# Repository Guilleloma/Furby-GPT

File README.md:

# Hacked Furby as a Desktop Assistant with Voice Control

https://github.com/Guilleloma/Furby-GPT/assets/115458145/2f7d8e4b-0d95-4262-baf4-6ca00bf8f71c

## Description
This project transforms a 1998 Furby into an interactive and advanced desktop assistant using a Raspberry Pi W. It incorporates OpenAI and Google Speech to text for natural language processing, primarily relying on Google Cloud Text to Speech for voice generation. It uses Picovoice's Porcupine library for voice activation and controls the Furby's motor for a dynamic user experience.

> **More on the web:** the [project page](https://makerisland.es/projects/furby-gpt) tells the full story, and [FurbyBoard por dentro](https://makerisland.es/projects/furby-gpt/placa) (in Spanish) is an interactive walkthrough of the custom board: every block animated, simulated signals and how to diagnose faults. The board's design files and datasheet live in [`Hardware/FurbyBoard/`](Hardware/FurbyBoard/README.md).

## Features
- **Function:** Designed to act as an interactive desktop assistant.
- **Platform:** Operates on a Raspberry Pi W.
- **Motor Control:** Animates the Furby in response to voice interactions.
- **Intelligent Interaction:** Processes natural language using OpenAI and Whisper/Google Speech to Text.
- **Voice Generation:** Primarily uses Google Cloud Text to Speech for verbal responses.
- **Voice Activation:** Utilizes Picovoice's Porcupine for detecting wake words.

## Requirements
- A 1998-2000 Furby.
- Raspberry Pi W (with necessary accessories).
- HAT Audio: WM8960 Audio HAT
- L298N H-Bridge (motor driver)
- Speaker (default speaker is useful as well but very poor)
- Access to OpenAI, Google Cloud & Picovoice (Elevenlabs optional)
- Knowledge in programming and electronics.

## Setup and Installation
1. **Hardware Preparation:** Modification and integration of the Raspberry Pi W into the Furby.
2. **Software Configuration:**
   - Installation and setup of OpenAI, Google Cloud
   - Installation of dependencies. Example:
     ```
     pip install openai whisper google-cloud-texttospeech pvporcupinewrapper python-dotenv
     ```
   - Add YOUR API Keys (see **Configuration** below)
3. **Programming and Integration:** Development of code to manage voice interaction and movement.

## Configuration
API keys are read from environment variables. Copy `.env.example` to `.env` and fill it in:
```
cp .env.example .env
```

| Variable | Required | Service |
|----------|----------|---------|
| `OPENAI_API_KEY` | Yes | OpenAI (Whisper and ChatGPT) |
| `PICOVOICE_ACCESS_KEY` | Yes | Picovoice Porcupine (wake word) |
| `GOOGLE_APPLICATION_CREDENTIALS` | Yes | Path to your Google Cloud service account JSON (Text-to-Speech) |
| `PICOVOICE_KEYWORD_PATH` | No | Path to your wake word model (`.ppn`). Defaults to `heymatepicovoice.ppn` next to the scripts |
| `ELEVENLABS_API_KEY` | Only with ElevenLabs | ElevenLabs (optional TTS) |
| `ELEVENLABS_VOICE_ID` | Only with ElevenLabs | ID of the ElevenLabs voice to use |

`.env` is loaded automatically when `python-dotenv` is installed; otherwise export the variables in your shell. `.env` is in `.gitignore`: never commit it. If a variable is missing, the program stops and tells you which one.

The wake word model is created in the Picovoice Console and is tied to your account, so `*.ppn` files are not committed: download yours and place it next to the scripts or set `PICOVOICE_KEYWORD_PATH`.

### Furby personality
The system prompt lives in `chatbot1.txt`, which is local and ignored by git. Create it from the example and personalise it:
```
cp chatbot1.example.txt chatbot1.txt
```
If `chatbot1.txt` does not exist, the program uses `chatbot1.example.txt` and prints a warning. Keep personal details in `chatbot1.txt` only.

## Usage
1. Wake up the Furby with a keyword using Porcupine.
2. Interact with the Furby, which uses Whisper and OpenAI for understanding and responding.
3. Enjoy the Furby's responses and animations, controlled by the Raspberry Pi W.

## Contribution
To contribute to the project:
```
1. Fork the project
2. Create your feature branch (`git checkout -b feature/AmazingFeature`)
3. Commit your changes (`git commit -m 'Add some AmazingFeature'`)
4. Push to the branch (`git push origin feature/AmazingFeature`)
5. Open a Pull Request
```

## License
This project is licensed under the MIT License - see the LICENSE.md file for details.

## Contact
Contact information of the project creator.

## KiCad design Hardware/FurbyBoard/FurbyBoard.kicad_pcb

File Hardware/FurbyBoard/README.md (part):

# FurbyBoard v1.0: hoja de datos

> **Explicación interactiva de cada bloque, con señales y diagnóstico:** [makerisland.es/projects/furby-gpt/placa](https://makerisland.es/projects/furby-gpt/placa)

Placa principal del Furby-GPT: va atornillada en el suelo de la base de un Furby de 1998 y sustituye a su electrónica. Lleva un ESP32-S3 con WiFi, cámara, micro y altavoz, mueve el motor original del mecanismo, lee los sensores del muñeco y se alimenta de una LiPo de una celda que se carga por USB-C.

Este documento es la referencia para quien coja la placa sin contexto: qué hace cada bloque, qué hay en cada conector, qué pin usa el firmware, dónde se mide y qué límites tiene. El porqué de cada decisión está en [`NOTAS.md`](NOTAS.md); el plan de pruebas, en [`TEST-PLAN.md`](TEST-PLAN.md); las simulaciones, en [`sim/RESULTADOS.md`](sim/RESULTADOS.md). Si este documento y el esquema no coinciden, manda el esquema (`scripts/design.py`).

## Estado (2026-10-27)

| | |
|---|---|
| Versión | **v1.0** (serigrafía «v1.0 · 2026-10») |
| Rama | `feature/electronica-v1` |
| Esquema | 8 hojas, 152 referencias (126 piezas montadas por el fabricante, 52 códigos LCSC). ERC 0 errores y 0 avisos |
| PCB | 6 capas, **rutada al completo** (0 conexiones sin unir). DRC con paridad esquema-PCB: 0 errores, 0 avisos. `pcb-toolkit revisar-rutado`: PASS, 0 errores |
| Puertas pasadas | A (arquitectura), B (esquema), C (colocación, con revisión independiente), D (rutado, propia), S (serigrafía), **E1** (diseño listo para fabricar, con revisión independiente) y **E2** (ficheros de fabricación). El 2026-10-27 se cerraron las mejoras **M7** (series de 33 Ω en los relojes de la cámara) y **M1** (paralelos In2/In3) con la E1 y la E2 repetidas (`revisiones/2026-10-27-M7-M1.md`); **pendiente su revisión independiente**. Informes en [`revisiones/`](revisiones/) y tabla «Revisiones» de `NOTAS.md` |
| Ficheros de fabricación | Gerber, taladros, BOM y CPL de JLCPCB en [`fabricacion/`](fabricacion/README.md), con la puerta E2 pasada (2026-10-25) y regenerados el 2026-10-27 tras M7 y M1. Antes de pedir: lista «Confirmar antes de pedir» de [`fabricacion/README.md`](fabricacion/README.md) |
| Fabricada | No. Nadie ha medido todavía una placa real: todo lo que sigue es diseño y simulación |
| Firmware | No existe. Las reglas que debe cumplir están en «Reglas para el firmware» |

## Resumen

| Característica | Valor |
|----------------|-------|
| Tamaño | ≈ 68,8 × 74,6 mm, forma del suelo de la base; 1,6 mm de grosor |
| Fijación | 4 tornillos M2 (taladros de 2,3 mm); agujero central de Ø11,3 mm para el eje del mecanismo |
| Alimentación | USB-C de 5 V (solo carga, Rd de 5,1 kΩ) y LiPo 1S de 1400 mAh soldada a pads, con protección contra la inversión |
| Carga | BQ24073 con power path: 0,49 A de carga; entrada de 0,475 A (USB500, por defecto) o 1,34 A (ILIM) |
| Raíles | VSYS (4,4 V con USB; VBAT − 50 mV sin USB), 3V3 (2 A), V6 (5,94 V para el motor), 2V8 y 1V2 de la cámara |
| Procesador | ESP32-S3-WROOM-1-N16R8 (16 MB de flash, 8 MB de PSRAM octal), WiFi y BLE con antena de PCB |
| Motor | Puente H DRV8231A a 6 V, PWM de 20 kHz, corriente limitada a 1,0 A y medida (2,25 V/A) |
| Audio | Amplificador clase D MAX98357A (altavoz de 4 Ω, 0,9–1,9 W según la batería) y micro I2S ICS-43434 en una plaquita aparte |
| Cámara | DVP de 8 bits por FPC de 24 pines (OV2640; OV3660 u OV5640 cambiando U9), con 33 Ω en serie en XCLK (R59, junto al módulo) y en PCLK (R60, junto al FPC) |
| Sensores | Inclinación, lengua, barriga y espalda por un expansor TCA9535; leva y encoder del mecanismo, luz e infrarrojos directos al módulo |
| Depuración | 5 LED, 14 puntos de test, botones RST y BOOT, consola UART en J_EXP y 5 puentes de soldadura |
| Consumo | Dormido ≈ 80 µA; escuchando 85–120 mA; pico ≈ 2,9 A en la batería (estimado) |
| Temperatura | 0–50 °C de ambiente dentro del Furby |

## Diagrama de bloques

```
USB-C (J1) ─ ESD USBLC6 (U1) ─ PTC 1,5 A (F1) ─ VBUS ─┐
                                                       │
                          BQ24073 (U2), power path ◄───┘
                          │  BAT ◄──► Q1 SI7615ADN ◄──► J2 (BAT+) / J3 (BAT−)  LiPo 1S
                          ▼
                        VSYS 4,4 V / VBAT
        ┌──────────────┬──────┴──────────┬───────────────────┬────────────┐
        ▼              ▼                 ▼                   ▼            ▼
  TPS63802 (U3)   TPS61089 (U5)    MAX98357A (U7)     LED IR (J7)    J_EXP.3
  buck-boost      elevador          clase D → J8        por R54 y Q3
  3V3, 2 A        V6 5,94 V         (altavoz)
        │              │
        │              └─► DRV8231A (U6) → motor (J9 M1/M2)
        ├─► ESP32-S3-WROOM-1 (U4) ── I2C ── TCA9535 (U10) ── sensores (J8, J9), LED RUN, LED del encoder (EN_6V por R51), control de la potencia
        │                         ├─ I2S ── U7 y micro (J5)
        │                         ├─ DVP ── cámara (J6)
        │                         └─ USB ── J1
        ├─► ME6211 2V8 (U8) → ME6211 1V2 (U9) → cámara (J6), encendidas por el expansor
        └─► pull-ups, LED, Schmitt del encoder (U11), J_EXP.2
```

| Bloque | Piezas | Qué hace |
|--------|--------|----------|
| Entrada USB | J1, U1, F1, R1, R2 | USB-C de 16 pines de montaje medio. Rd de 5,1 kΩ en CC1 y CC2: cualquier fuente da 5 V. **La placa no lee las líneas CC**, así que no sabe cuánta corriente ofrece el cargador. D+ y D− van al USB nativo del ESP32-S3 |
| Cargador y power path | U2, R4–R7, C1–C4, RT1 | BQ24073: carga a 0,494 A (R4) con ventana de temperatura de 0–50 °C medida por la NTC RT1 bajo la batería. Arranca en USB500 (EN1 = 1, EN2 = 0); el firmware puede pasar a ILIM (1,34 A, R5). VSYS sale regulado a 4,4 V con USB y sigue a la batería sin él |
| Batería | J2, J3, Q1, R12, R13, R14, C5 | P-MOSFET SI7615ADN con la puerta a GND: con la batería al revés no llega tensión negativa a nada (probado también con USB en la simulación). Divisor 470k/470k a VBAT_SNS (ADC) |
| 3V3 | U3, L1, R15, R16, C6–C8 | Buck-boost TPS63802: 3,30 V desde VSYS (2,3–4,4 V), hasta 2 A; alimenta el módulo, el expansor, la cámara y la lógica |
| 6 V y motor | U5, L2, R20–R25, C12–C22, U6, R26–R30, JP1–JP3 | Elevador TPS61089 a 5,94 V (ILIM 3,8 A), solo encendido cuando hace falta (EN_6V). Puente H DRV8231A con ITRIP de 1,0 A (VREF por R26/R27) y salida de corriente IPROPI (2,25 V/A, R28) al ADC |
| Audio | U7, C24–C26, C41, R31, R32, J5 | MAX98357A desde VSYS, ganancia de 6 dB, controlado por AMP_SD. El micro ICS-43434 va en una plaquita con cable (≤ 15 cm) a J5; comparte BCLK y WS con el amplificador (bus I2S full duplex) |
| Cámara | J6, U8, U9, R33–R35, R59, R60, C27–C31 | FPC de 24 pines con el pinout habitual de los módulos OV2640/OV3660/OV5640 para ESP32 (**verificar con el módulo concreto**). AVDD de 2,8 V y DVDD de 1,2 V (1,5 V cambiando U9 por ME6211C15) con CAM_EN; DOVDD a 3V3 |
| Expansor y sensores | U10, R36–R52, C32–C39, U11, JP4 | TCA9535 en 0x20 sobre el I2C del módulo (el mismo bus que el SCCB de la cámara). Entradas con pull-up, 1 kΩ en serie y 100 nF; Schmitt 74LVC1G17 para el encoder |
| IR y luz | Q3, R53–R56, C40, J7 | Emisor IR con AO3400A (≈ 100 mA en pulsos por R54 de 22 Ω desde VSYS), receptor alimentado por el expansor (P17), LDR con 470 kΩ a GND |
| LED y depuración | D1–D5, R10, R11, R19, R57, R58, SW1, SW2, JP5, TP1–TP14, J11 | Ver «LED», «Botones y puentes» y «Puntos de test» |

## Capas y rutado

**6 capas, 1,6 mm, apilado JLC06161H-7628 de JLCPCB** (cobre de 1 oz fuera y 0,5 oz dentro; espesores a confirmar en el presupuesto del pedido):

| Capa | Uso | Dieléctrico debajo |
|------|-----|--------------------|
| L1 F.Cu | Todas las piezas, par USB (0,28/0,15 mm, ≈ 87 Ω diferencial) y bus de la cámara sobre GND; relleno de GND | prepreg 0,21 mm |
| L2 In1 | **GND continuo** (salvo bajo la antena) | núcleo 0,40 mm |
| L3 In2 | Señales (I2S, sensado, señales lentas bajo el módulo) con relleno de VSYS | prepreg 0,21 mm |
| L4 In3 | Señales lentas: autopistas este-oeste y norte-sur (expansor, J9, UART, IR, I2C a J_EXP) | núcleo 0,40 mm |
| L5 In4 | **GND continuo** (referencia de In3 y de B.Cu) | prepreg 0,21 mm |
| L6 B.Cu | Señales, TP, pads de cable y relleno de GND; logos y rótulos | — |

Vías pasantes de 0,6/0,3 mm (0,45/0,2 solo en el par USB); sin ciegas ni enterradas. Las vías térmicas de los pads expuestos (U2, U4, U6, U7) van rellenas y tapadas (POFV, de serie en 6 capas en JLCPCB). Toda la placa está cosida a GND entre In1, In4 y las caras exteriores (paso de ≈ 4 mm en el borde).

**Por qué 6 y no 4:** con 4 capas, el rutado crítico (lazos de los convertidores, par USB, bus de la cámara, I2S) y la colocación aprobada dejaban encerrado al expansor: 57 conexiones no tenían camino. Pasar a 6 capas (In3 de señal e In4 de GND) conservó todo lo rutado y abrió los pasillos; cuesta del orden de 15–30 USD más por pedido de 5 placas (decisión del autor del proyecto, 2026-10-24).

**Cómo está rutada:** a mano, por bloques de señales, en [`scripts/rutas_fijas.py`](scripts/rutas_fijas.py): cada pista, vía y polígono está escrito con su red, su capa y su ancho, y `gen_pcb.py` lo resuelve contra los pads reales. **No hay autorrutador** (Freerouting se probó con la colocación de 4 capas y se descartó). Lo primero fueron los lazos de potencia según el layout de referencia de cada chip, el par USB, la cámara y el I2S; después, las señales lentas por bloques (A1…U2), los arreglos de la simulación (bloque F), el cosido de GND (bloque E) y la serigrafía (bloque S). Anchos mínimos por red (tabla de raíles de `NOTAS.md`) comprobados por el DRC y por `revisar-rutado`.

## Serigrafía

- **Cara superior:** qué es cada LED, botón y puente, y «FURBYBOARD V1.0».
- **Cara inferior:** la función de cada pad de cable y los GPIO de J_EXP, el nombre de cada TP, «FurbyBoard», versión y fecha, el recuadro PLACA para numerarla y dos logos: el Furby en pixel art (esquina trasera, junto a J_EXP) y el de **@GuilleMaker** (11,0 × 10,7 mm, sobre el nombre de la placa, junto al agujero del mecanismo).
- Los rótulos y el logo de GuilleMaker se colocan por script **después del rutado**, sin pisar vías (≥ 0,15 mm), pads ni otros rótulos; el logo va el último porque es decoración. Letra de 1,0 mm (0,8 donde no cabe, ver «Limitaciones conocidas») y trazo de 0,15 mm, los mínimos de JLCPCB.
- Logo de GuilleMaker: [`scripts/logo_guillemaker.py`](scripts/logo_guillemaker.py) lo vectoriza desde [`serigrafia/logo-guillemaker.png`](serigrafia/logo-guillemaker.png); el texto mide 1,48 mm de alto con trazo de 0,18 mm. Vista de la cara inferior: [`render/serigrafia-logo-guillemaker.png`](render/serigrafia-logo-guillemaker.png).

## Conectores y pads

Las vistas «desde abajo» son como se ve la placa por la cara inferior, donde se sueldan los cables. Los pads de cable son pasantes de 2,54 mm; el pad 1 es el cuadrado.

### J1: USB-C (16 pines, HRO TYPE-C-31-M-13C)

| Pin | Red | Notas |
|-----|-----|-------|
| A4, A9, B4, B9 | VBUS_IN | 5 V; pasa por U1 (ESD) y F1 (PTC de 1,5 A) a VBUS |
| A5 / B5 | CC1 / CC2 | Rd de 5,1 kΩ a GND (R1, R2): sumidero por defecto |
| A6, B6 / A7, B7 | USB_DP / USB_DN | USB nativo del ESP32-S3 (GPIO20/19, USB Serial/JTAG); protegidos por U1 |
| A1, A12, B1, B12, carcasa | GND | |
| A8, B8 | — | SBU sin conectar |

### J2 y J3: batería

| Pad | Forma | Red | Rótulos |
|-----|-------|-----|---------|
| J2 | Cuadrado de 3 × 3 mm, taladro de 1,2 | BAT_PAD (+), antes de Q1 | «+» arriba, «BAT+» abajo |
| J3 | Redondo de Ø2,6 mm, taladro de 1,0 | GND (−) | «-» arriba, «BAT-» abajo |

Celda LiPo 1S de 1400 mAh **con PCM** y resistencia interna (con el PCM) **≤ 100 mΩ** («Reglas para el firmware»). Antes de soldarla se prueba la protección contra la inversión (`TEST-PLAN.md` §8.1).

### J5: micro I2S (2 × 3, en el borde izquierdo)

| Pad | Rótulo | Red | Pin del micro |
|-----|--------|-----|---------------|
| 1 | SD | I2S_DIN (GPIO17) | SD (datos) |
| 2 | G | GND | GND |
| 3 | SCK | I2S_SCK_MIC (BCLK por R31 de 33 Ω) | SCK |
| 4 | WS | I2S_WS_MIC (WS por R32 de 33 Ω) | WS |
| 5 | 3V3 | 3V3 | VDD |
| 6 | G | GND | GND (y L/R, según el canal elegido en la plaquita) |

La selección L/R del ICS-43434 se fija en la plaquita del micro. Cable de ≤ 15 cm.

### J6: cámara (FPC de 24 pines, paso 0,5 mm, AFC01-S24FCA-00)

En el borde derecho, pin 1 abajo, con el flex saliendo hacia la pared de la base.

| Pin | Red | Pin | Red |
|-----|-----|-----|-----|
| 1 | — | 13 | CAM_XCLK (GPIO13 por R59 de 33 Ω) |
| 2 | GND | 14 | CAM_Y8 (GPIO14) |
| 3 | I2C_SDA (SIOD) | 15 | GND |
| 4 | CAM_2V8 (AVDD) | 16 | CAM_Y7 (GPIO21) |
| 5 | I2C_SCL (SIOC) | 17 | CAM_PCLK_CAM (GPIO47 por R60 de 33 Ω) |
| 6 | CAM_RST (RC de R35/C31) | 18 | CAM_Y6 (GPIO48) |
| 7 | CAM_VSYNC (GPIO10) | 19 | CAM_Y2 (GPIO38) |
| 8 | CAM_PWDN (P15 del expansor) | 20 | CAM_Y5 (GPIO39) |
| 9 | CAM_HREF (GPIO11) | 21 | CAM_Y3 (GPIO40) |
| 10 | CAM_DVDD (1,2 V) | 22 | CAM_Y4 (GPIO41) |
| 11 | 3V3 (DOVDD) | 23, 24 | — |
| 12 | CAM_Y9 (GPIO12) | Patas | GND |

Pinout de facto de los módulos para ESP32 (OV2640/OV3660/OV5640): **compruébese con el módulo comprado antes de enchufarlo**. RESETB no da un flanco limpio al encender: el firmware resetea la cámara por SCCB.

### J7: IR y luz (2 × 4, delante a la izquierda)

| Pad | Rótulo | Red | Qué se conecta |
|-----|--------|-----|----------------|
| 1 | IR+ | IR_LED_A (VSYS por R54 de 22 Ω) | Ánodo del LED IR emisor |
| 2 | IR- | IR_LED_K (drenador de Q3, GPIO45) | Cátodo del LED IR emisor |
| 3 | G | GND | GND del receptor IR |
| 4 | RX | IR_RX_PAD (GPIO42 por R56 de 1 kΩ) | Salida del receptor IR |
| 5 | 3V3 | 3V3 | Un extremo de la LDR |
| 6 | LDR | LIGHT (GPIO2, 470 kΩ a GND) | Otro extremo de la LDR |
| 7 | G | GND | |
| 8 | RXV | IR_PWR (P17 del expansor) | Alimentación del receptor IR (se apaga para dormir) |

Leyenda en la cara inferior a la derecha de los pads, fila por fila. J7.3 y J7.8 se permutaron en el rutado (bloque U2): el receptor IR usa 8 (alimentación), 3 (GND) y 4 (salida).

### J8: inclinación, lengua y altavoz (1 × 7, borde izquierdo)

| Pad | Rótulo | Red | Qué se conecta |
|-----|--------|-----|----------------|
| 1 | TLA | TILT_A_PAD (P00, 220 kΩ de pull-up) | Contacto A del sensor de inclinación |
| 2 | TLB | TILT_B_PAD (P01, 220 kΩ) | Contacto B del sensor de inclinación |
| 3 | G | GND | Común del sensor de inclinación |
| 4 | LNG | TONGUE_PAD (P02, 47 kΩ) | Interruptor de la lengua |
| 5 | G | GND | Otro lado del interruptor de la lengua |
| 6 | SP+ | SPK_P | Altavoz + (4 Ω) |
| 7 | SP- | SPK_N | Altavoz − |

Las salidas del altavoz son las del clase D en puente (BTL): ninguna de las dos va a GND.

### J9: mecanismo, barriga y espalda (2 × 6, borde derecho)

| Pad | Rótulo | Red | Qué se conecta |
|-----|--------|-----|----------------|
| 1 | ENF | ENC_PT (10 kΩ a 3V3, Schmitt U11 → GPIO8) | Colector del fototransistor del encoder |
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
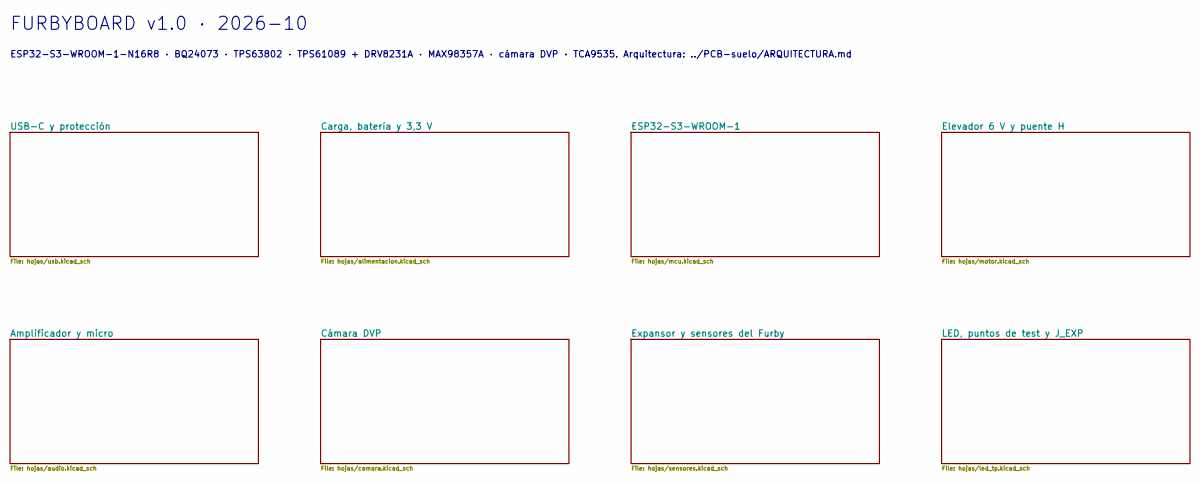
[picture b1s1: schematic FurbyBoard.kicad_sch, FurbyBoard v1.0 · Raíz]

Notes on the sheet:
FURBYBOARD v1.0 · 2026-10
ESP32-S3-WROOM-1-N16R8 · BQ24073 · TPS63802 · TPS61089 + DRV8231A · MAX98357A · cámara DVP · TCA9535. Arquitectura: ../PCB-suelo/ARQUITECTURA.md

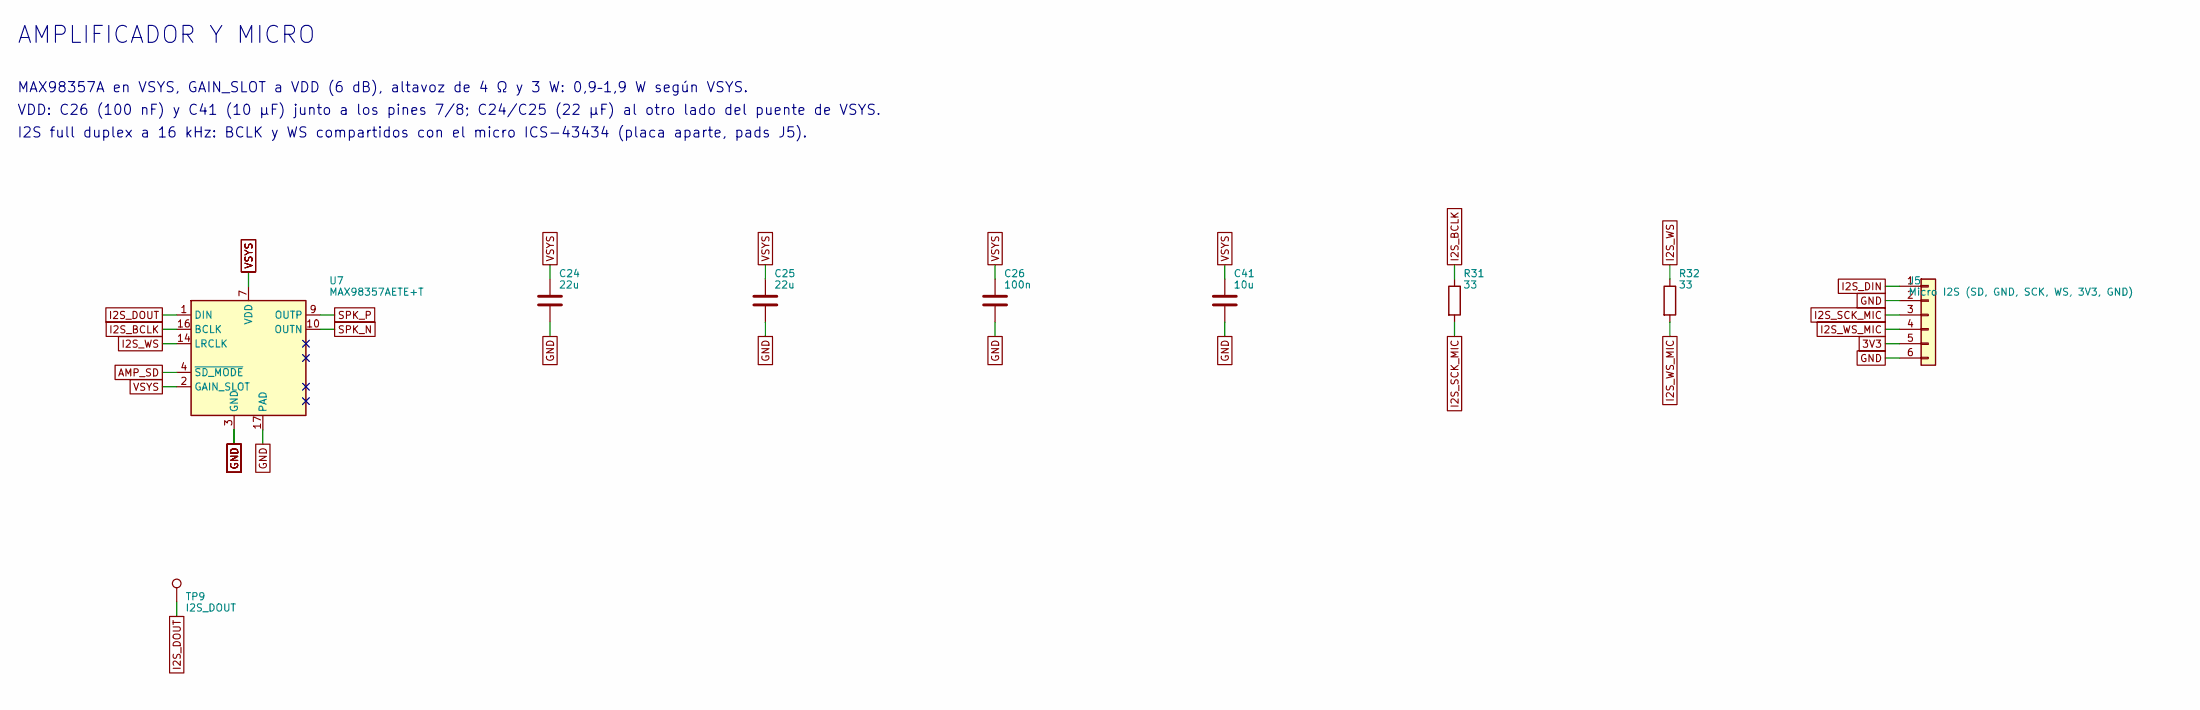
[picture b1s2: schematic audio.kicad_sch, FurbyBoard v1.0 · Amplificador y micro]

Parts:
C24, C25: 22u; C_0805_2012Metric; MPN 22 µF 25 V X5R; LCSC C45783
C26: 100n; C_0603_1608Metric; MPN 100 nF 50 V X7R; LCSC C14663
C41: 10u; C_0603_1608Metric; MPN 10 µF 10 V X5R; LCSC C19702
J5: Micro I2S (SD, GND, SCK, WS, 3V3, GND); Pads_2x03_P2.54mm
R31, R32: 33; R_0603_1608Metric; MPN UNI-ROYAL 0603 1%; LCSC C23140
TP9: I2S_DOUT; TestPoint_Pad_D1.5mm
U7: MAX98357AETE+T; TQFN-16-1EP_3x3mm_P0.5mm_EP1.23x1.23mm; MPN Maxim MAX98357AETE+T; LCSC C910544

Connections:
3V3: J5.5; also elsewhere on the board
AMP_SD: U7.4 (~SD_MODE); also elsewhere on the board
GND: C24.2, C25.2, C26.2, C41.2, J5.2, J5.6, U7.3 (GND), U7.11 (GND), U7.15 (GND), U7.17 (PAD); also elsewhere on the board
I2S_BCLK: R31.1, U7.16 (BCLK); also elsewhere on the board
I2S_DIN: J5.1; also elsewhere on the board
I2S_DOUT: TP9.1, U7.1 (DIN); also elsewhere on the board
I2S_SCK_MIC: J5.3, R31.2
I2S_WS: R32.1, U7.14 (LRCLK); also elsewhere on the board
I2S_WS_MIC: J5.4, R32.2
SPK_N: U7.10 (OUTN); also elsewhere on the board
SPK_P: U7.9 (OUTP); also elsewhere on the board
VSYS: C24.1, C25.1, C26.1, C41.1, U7.2 (GAIN_SLOT), U7.7 (VDD), U7.8 (VDD); also elsewhere on the board

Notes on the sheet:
VDD: C26 (100 nF) y C41 (10 µF) junto a los pines 7/8; C24/C25 (22 µF) al otro lado del puente de VSYS.
I2S full duplex a 16 kHz: BCLK y WS compartidos con el micro ICS-43434 (placa aparte, pads J5).
MAX98357A en VSYS, GAIN_SLOT a VDD (6 dB), altavoz de 4 Ω y 3 W: 0,9–1,9 W según VSYS.
AMPLIFICADOR Y MICRO

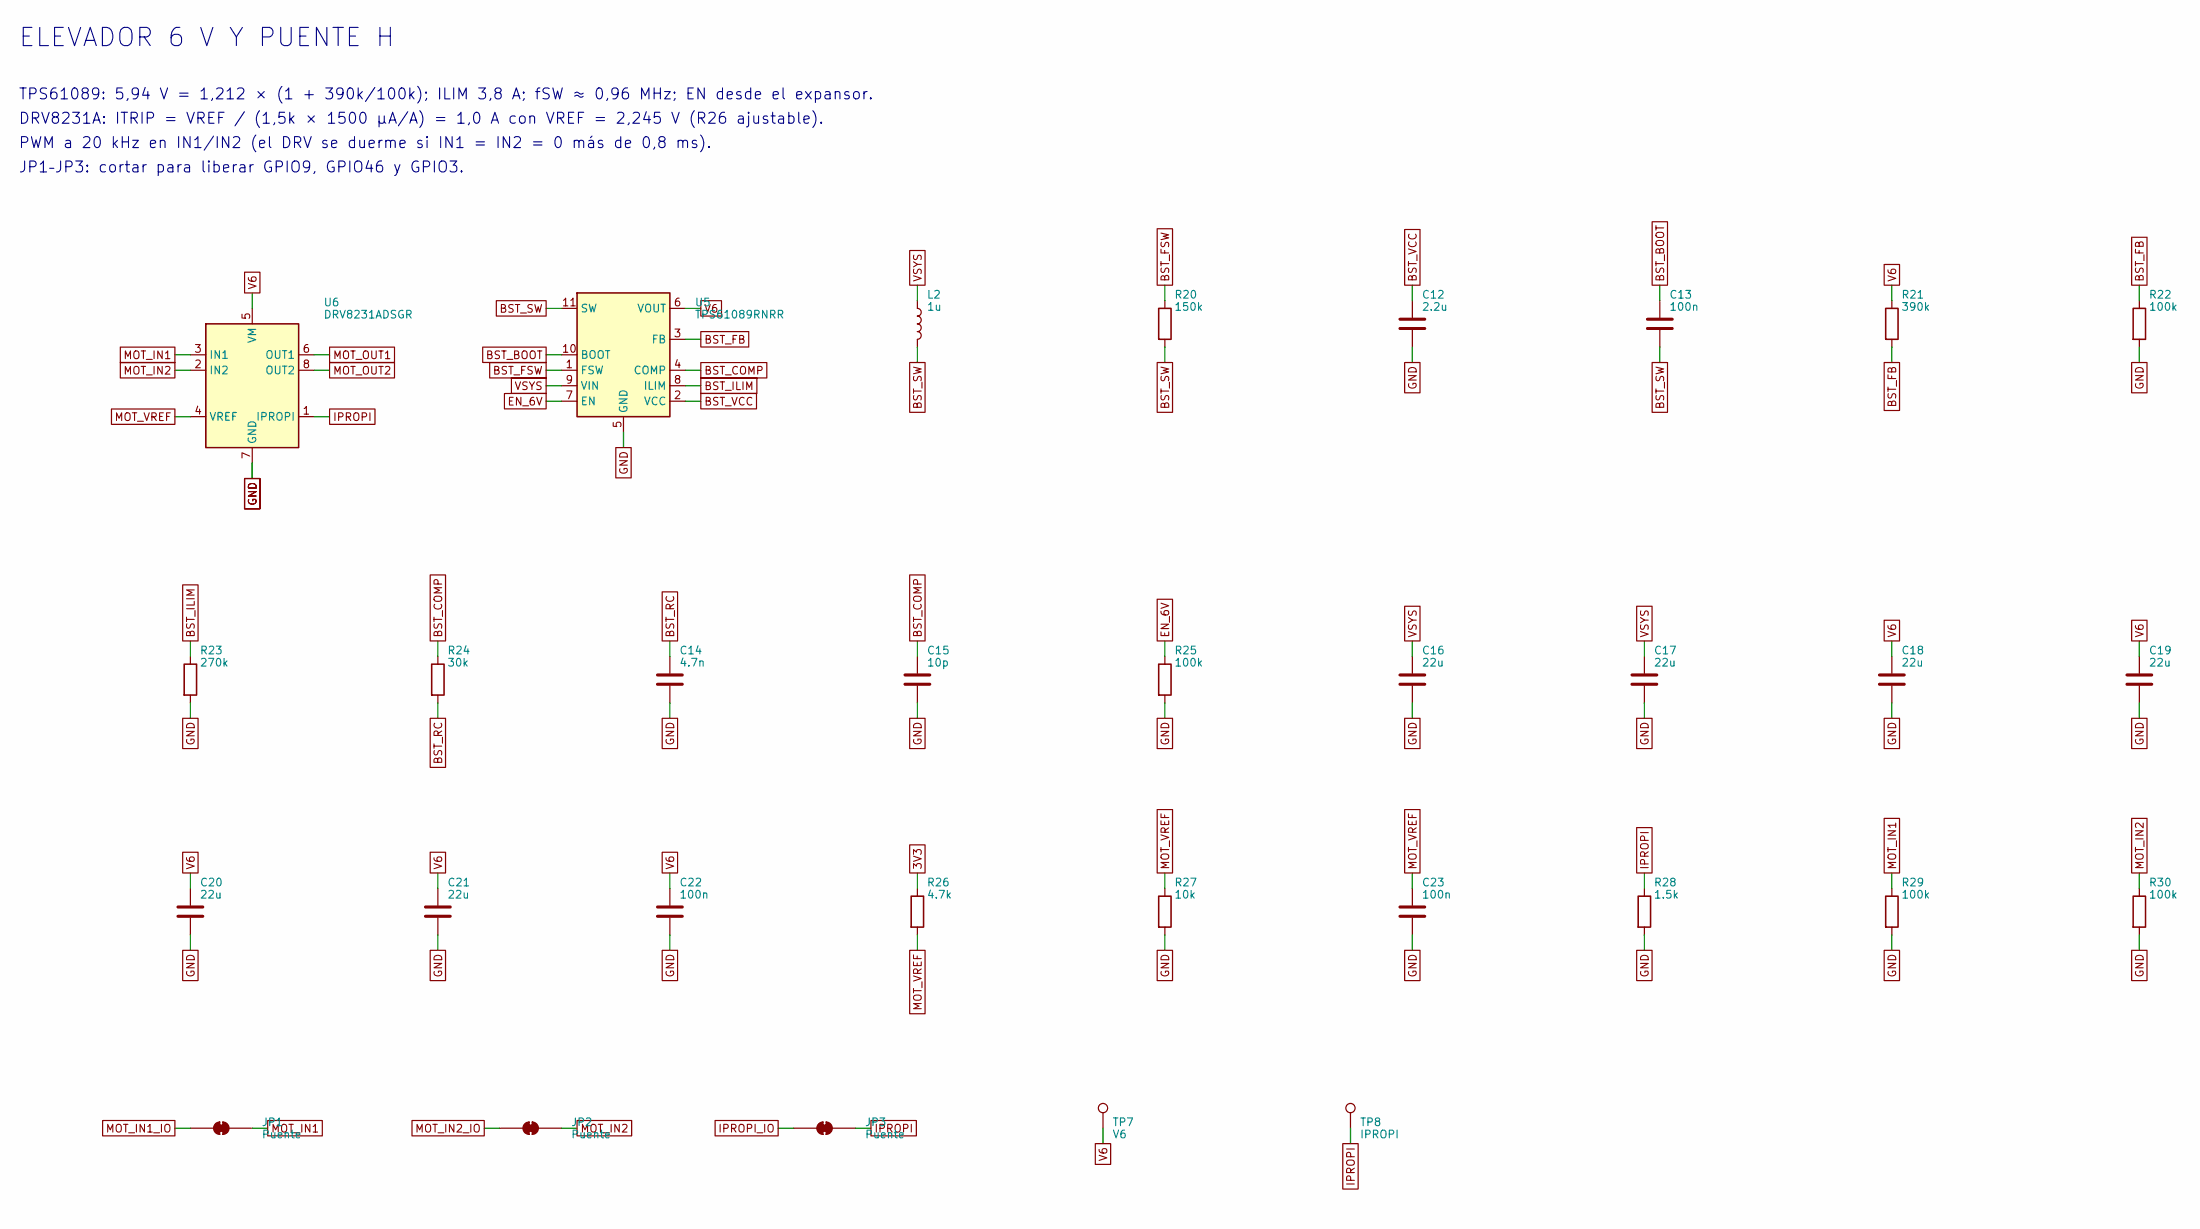
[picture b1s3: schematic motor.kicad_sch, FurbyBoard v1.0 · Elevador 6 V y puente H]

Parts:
C12: 2.2u; C_0603_1608Metric; MPN 2,2 µF 16 V X5R; LCSC C23630
C13, C22, C23: 100n; C_0603_1608Metric; MPN 100 nF 50 V X7R; LCSC C14663
C14: 4.7n; C_0603_1608Metric; MPN 4,7 nF 50 V X7R; LCSC C53987
C15: 10p; C_0603_1608Metric; MPN 10 pF 50 V C0G; LCSC C1634
C16, C17, C18, C19, C20, C21: 22u; C_0805_2012Metric; MPN 22 µF 25 V X5R; LCSC C45783
JP1, JP2, JP3: Puente; SolderJumper-2_P1.3mm_Bridged_RoundedPad1.0x1.5mm
L2: 1u; L_Changjiang_FHD4020S; MPN Changjiang FHD4020S-1R0MT; LCSC C602028
R20: 150k; R_0603_1608Metric; MPN UNI-ROYAL 0603 1%; LCSC C22807
R21: 390k; R_0603_1608Metric; MPN UNI-ROYAL 0603 1%; LCSC C23150
R22, R25, R29, R30: 100k; R_0603_1608Metric; MPN UNI-ROYAL 0603 1%; LCSC C25803
R23: 270k; R_0603_1608Metric; MPN UNI-ROYAL 0603 1%; LCSC C22965
R24: 30k; R_0402_1005Metric; MPN UNI-ROYAL 0402 1%; LCSC C25776
R26: 4.7k; R_0603_1608Metric; MPN UNI-ROYAL 0603 1%; LCSC C23162
R27: 10k; R_0603_1608Metric; MPN UNI-ROYAL 0603 1%; LCSC C25804
R28: 1.5k; R_0603_1608Metric; MPN UNI-ROYAL 0603 1%; LCSC C22843
TP7: V6; TestPoint_Pad_D1.5mm
TP8: IPROPI; TestPoint_Pad_D1.5mm
U5: TPS61089RNRR; Texas_VQFN-RNR0011A-11; MPN TI TPS61089RNRR; LCSC C165129
U6: DRV8231ADSGR; Texas_DSG0008A_WSON-8-1EP_2x2mm_P0.5mm_EP0.9x1.6mm; MPN TI DRV8231ADSGR; LCSC C5139865

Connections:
3V3: R26.1; also elsewhere on the board
BST_BOOT: C13.1, U5.10 (BOOT)
BST_COMP: C15.1, R24.1, U5.4 (COMP)
BST_FB: R21.2, R22.1, U5.3 (FB)
BST_FSW: R20.1, U5.1 (FSW)
BST_ILIM: R23.1, U5.8 (ILIM)
BST_RC: C14.1, R24.2
BST_SW: C13.2, L2.2, R20.2, U5.11 (SW)
BST_VCC: C12.1, U5.2 (VCC)
EN_6V: R25.1, U5.7 (EN); also elsewhere on the board
GND: C12.2, C14.2, C15.2, C16.2, C17.2, C18.2, C19.2, C20.2, C21.2, C22.2, C23.2, R22.2, R23.2, R25.2, R27.2, R28.2, R29.2, R30.2, U5.5 (GND), U6.7 (GND), U6.9 (GND); also elsewhere on the board
IPROPI: JP3.2 (B), R28.1, TP8.1, U6.1 (IPROPI)
IPROPI_IO: JP3.1 (A); also elsewhere on the board
MOT_IN1: JP1.2 (B), R29.1, U6.3 (IN1)
MOT_IN1_IO: JP1.1 (A); also elsewhere on the board
MOT_IN2: JP2.2 (B), R30.1, U6.2 (IN2)
MOT_IN2_IO: JP2.1 (A); also elsewhere on the board
MOT_OUT1: U6.6 (OUT1); also elsewhere on the board
MOT_OUT2: U6.8 (OUT2); also elsewhere on the board
MOT_VREF: C23.1, R26.2, R27.1, U6.4 (VREF)
V6: C18.1, C19.1, C20.1, C21.1, C22.1, R21.1, TP7.1, U5.6 (VOUT), U6.5 (VM)
VSYS: C16.1, C17.1, L2.1, U5.9 (VIN); also elsewhere on the board

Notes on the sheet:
JP1–JP3: cortar para liberar GPIO9, GPIO46 y GPIO3.
PWM a 20 kHz en IN1/IN2 (el DRV se duerme si IN1 = IN2 = 0 más de 0,8 ms).
TPS61089: 5,94 V = 1,212 × (1 + 390k/100k); ILIM 3,8 A; fSW ≈ 0,96 MHz; EN desde el expansor.
DRV8231A: ITRIP = VREF / (1,5k × 1500 µA/A) = 1,0 A con VREF = 2,245 V (R26 ajustable).
ELEVADOR 6 V Y PUENTE H

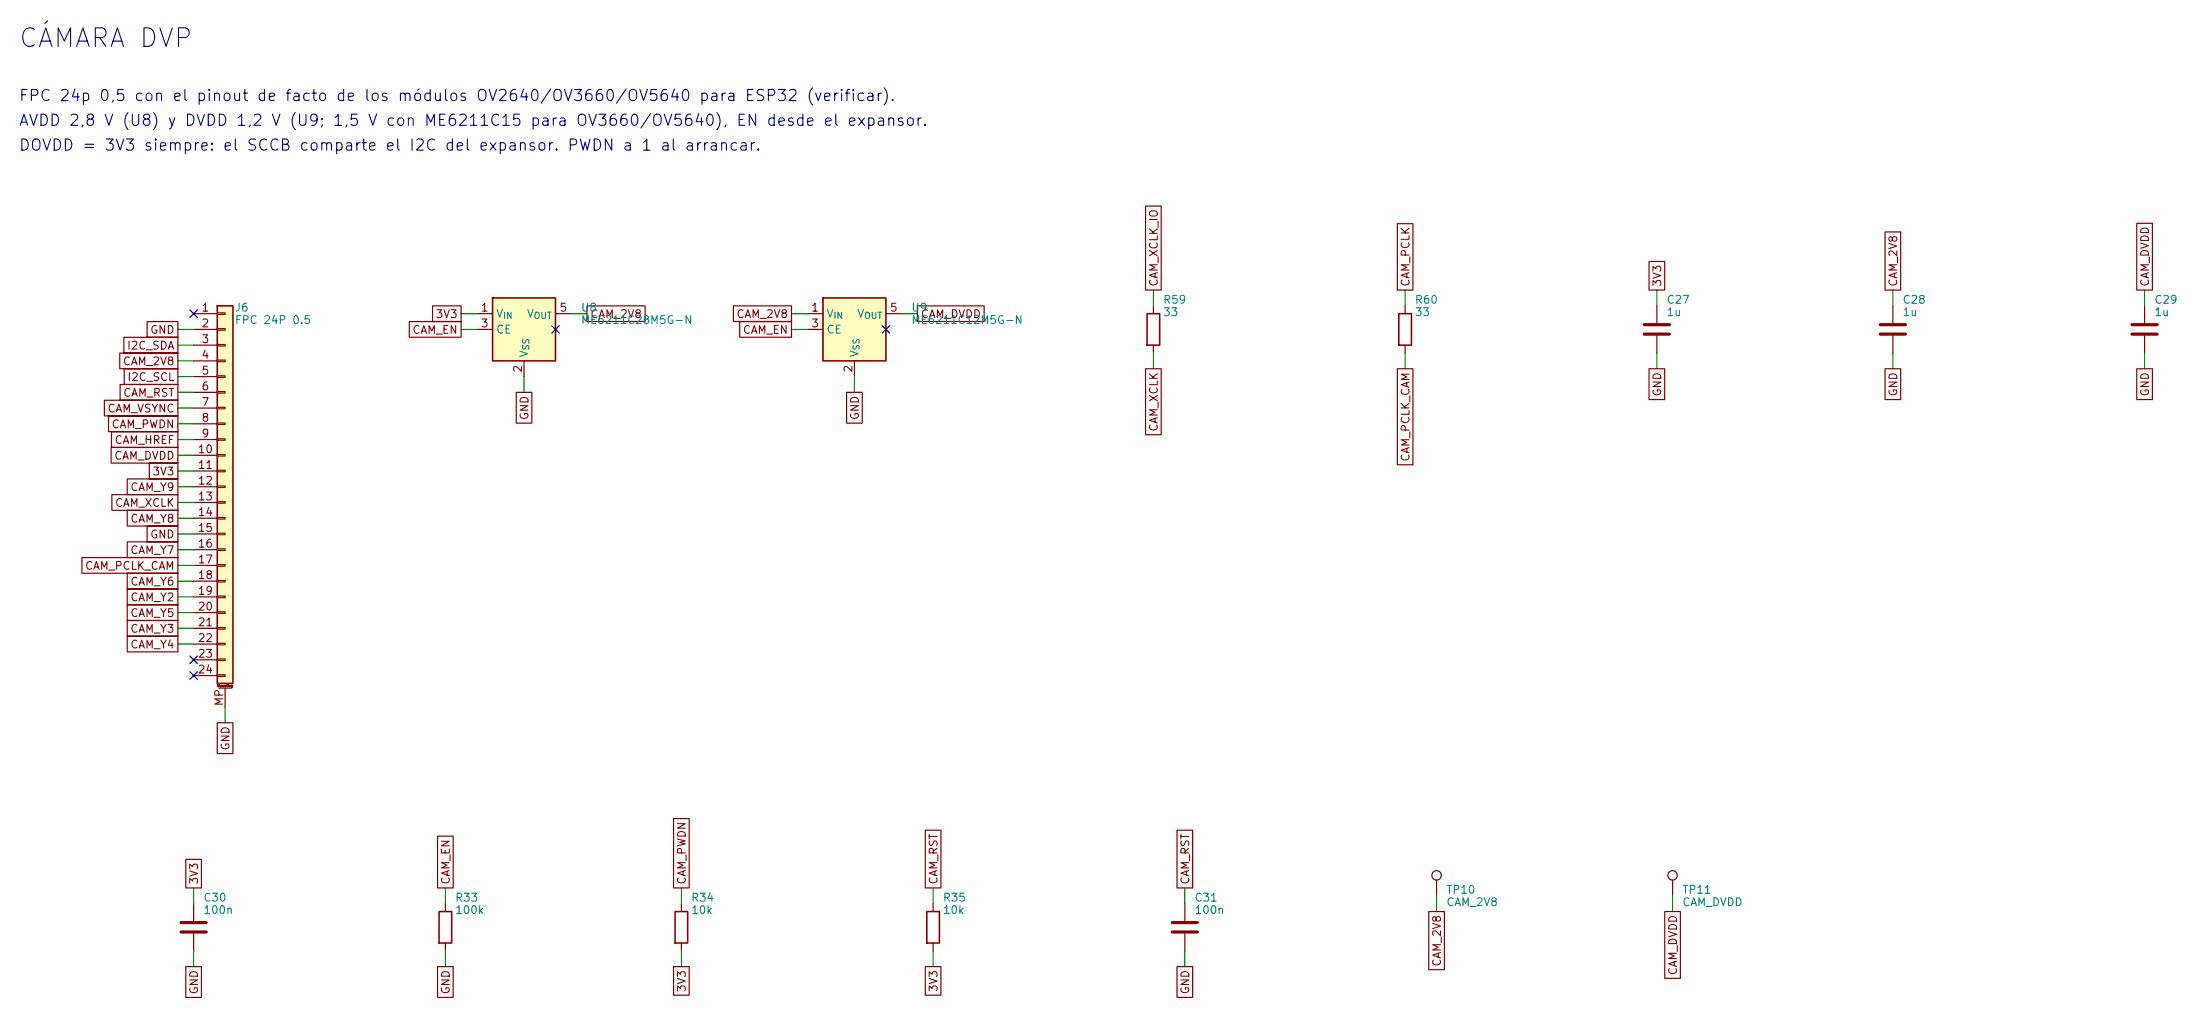
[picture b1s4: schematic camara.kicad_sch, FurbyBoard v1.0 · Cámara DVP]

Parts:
C27, C28, C29: 1u; C_0603_1608Metric; MPN 1 µF 50 V X5R; LCSC C15849
C30, C31: 100n; C_0603_1608Metric; MPN 100 nF 50 V X7R; LCSC C14663
J6: FPC 24P 0.5; FPC_AFC01-S24FCA-00; MPN JUSHUO AFC01-S24FCA-00; LCSC C262669
R33: 100k; R_0603_1608Metric; MPN UNI-ROYAL 0603 1%; LCSC C25803
R34, R35: 10k; R_0603_1608Metric; MPN UNI-ROYAL 0603 1%; LCSC C25804
R59, R60: 33; R_0402_1005Metric; MPN UNI-ROYAL 0402 1%; LCSC C25105
TP10: CAM_2V8; TestPoint_Pad_D1.5mm
TP11: CAM_DVDD; TestPoint_Pad_D1.5mm
U8: ME6211C28M5G-N; SOT-23-5; MPN Microne ME6211C28M5G-N; LCSC C53099
U9: ME6211C12M5G-N; SOT-23-5; MPN Microne ME6211C12M5G-N; LCSC C236672

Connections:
3V3: C27.1, C30.1, J6.11, R34.2, R35.2, U8.1 (V_{IN}); also elsewhere on the board
CAM_2V8: C28.1, J6.4, TP10.1, U8.5 (V_{OUT}), U9.1 (V_{IN})
CAM_DVDD: C29.1, J6.10, TP11.1, U9.5 (V_{OUT})
CAM_EN: R33.1, U8.3 (CE), U9.3 (CE); also elsewhere on the board
CAM_HREF: J6.9; also elsewhere on the board
CAM_PCLK: R60.1; also elsewhere on the board
CAM_PCLK_CAM: J6.17, R60.2
CAM_PWDN: J6.8, R34.1; also elsewhere on the board
CAM_RST: C31.1, J6.6, R35.1
CAM_VSYNC: J6.7; also elsewhere on the board
CAM_XCLK: J6.13, R59.2
CAM_XCLK_IO: R59.1; also elsewhere on the board
CAM_Y2: J6.19; also elsewhere on the board
CAM_Y3: J6.21; also elsewhere on the board
CAM_Y4: J6.22; also elsewhere on the board
CAM_Y5: J6.20; also elsewhere on the board
CAM_Y6: J6.18; also elsewhere on the board
CAM_Y7: J6.16; also elsewhere on the board
CAM_Y8: J6.14; also elsewhere on the board
CAM_Y9: J6.12; also elsewhere on the board
GND: C27.2, C28.2, C29.2, C30.2, C31.2, J6.2, J6.15, J6.MP (MountPin), R33.2, U8.2 (V_{SS}), U9.2 (V_{SS}); also elsewhere on the board
I2C_SCL: J6.5; also elsewhere on the board
I2C_SDA: J6.3; also elsewhere on the board

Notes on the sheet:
DOVDD = 3V3 siempre: el SCCB comparte el I2C del expansor. PWDN a 1 al arrancar.
CÁMARA DVP
FPC 24p 0,5 con el pinout de facto de los módulos OV2640/OV3660/OV5640 para ESP32 (verificar).
AVDD 2,8 V (U8) y DVDD 1,2 V (U9; 1,5 V con ME6211C15 para OV3660/OV5640), EN desde el expansor.

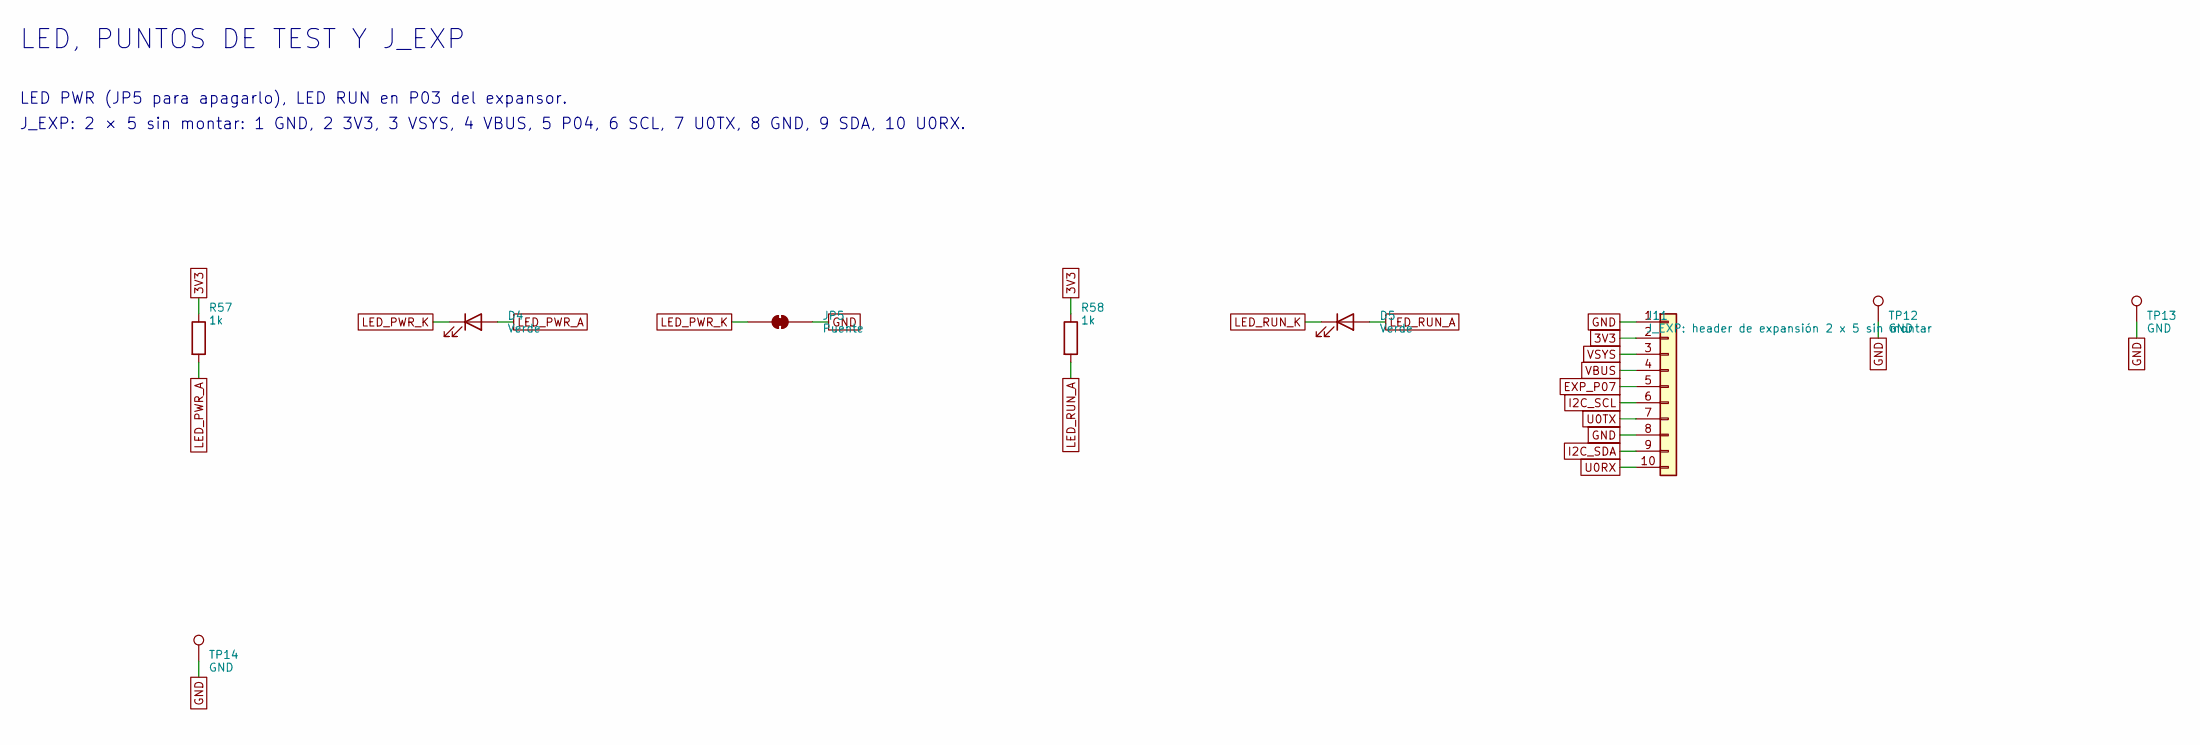
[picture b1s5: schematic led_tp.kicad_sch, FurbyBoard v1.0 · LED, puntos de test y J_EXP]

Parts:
D4, D5: Verde; LED_0805_2012Metric; MPN KT-0805G; LCSC C2297
J11: J_EXP: header de expansión 2 x 5 sin montar; Pads_2x05_P2.54mm
JP5: Puente; SolderJumper-2_P1.3mm_Bridged_RoundedPad1.0x1.5mm
R57, R58: 1k; R_0603_1608Metric; MPN UNI-ROYAL 0603 1%; LCSC C21190
TP12, TP13, TP14: GND; TestPoint_Pad_D1.5mm

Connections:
3V3: J11.2, R57.1, R58.1; also elsewhere on the board
EXP_P07: J11.5; also elsewhere on the board
GND: J11.1, J11.8, JP5.2 (B), TP12.1, TP13.1, TP14.1; also elsewhere on the board
I2C_SCL: J11.6; also elsewhere on the board
I2C_SDA: J11.9; also elsewhere on the board
LED_PWR_A: D4.2 (A), R57.2
LED_PWR_K: D4.1 (K), JP5.1 (A)
LED_RUN_A: D5.2 (A), R58.2
LED_RUN_K: D5.1 (K); also elsewhere on the board
U0RX: J11.10; also elsewhere on the board
U0TX: J11.7; also elsewhere on the board
VBUS: J11.4; also elsewhere on the board
VSYS: J11.3; also elsewhere on the board

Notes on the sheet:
J_EXP: 2 × 5 sin montar: 1 GND, 2 3V3, 3 VSYS, 4 VBUS, 5 P04, 6 SCL, 7 U0TX, 8 GND, 9 SDA, 10 U0RX.
LED, PUNTOS DE TEST Y J_EXP
LED PWR (JP5 para apagarlo), LED RUN en P03 del expansor.

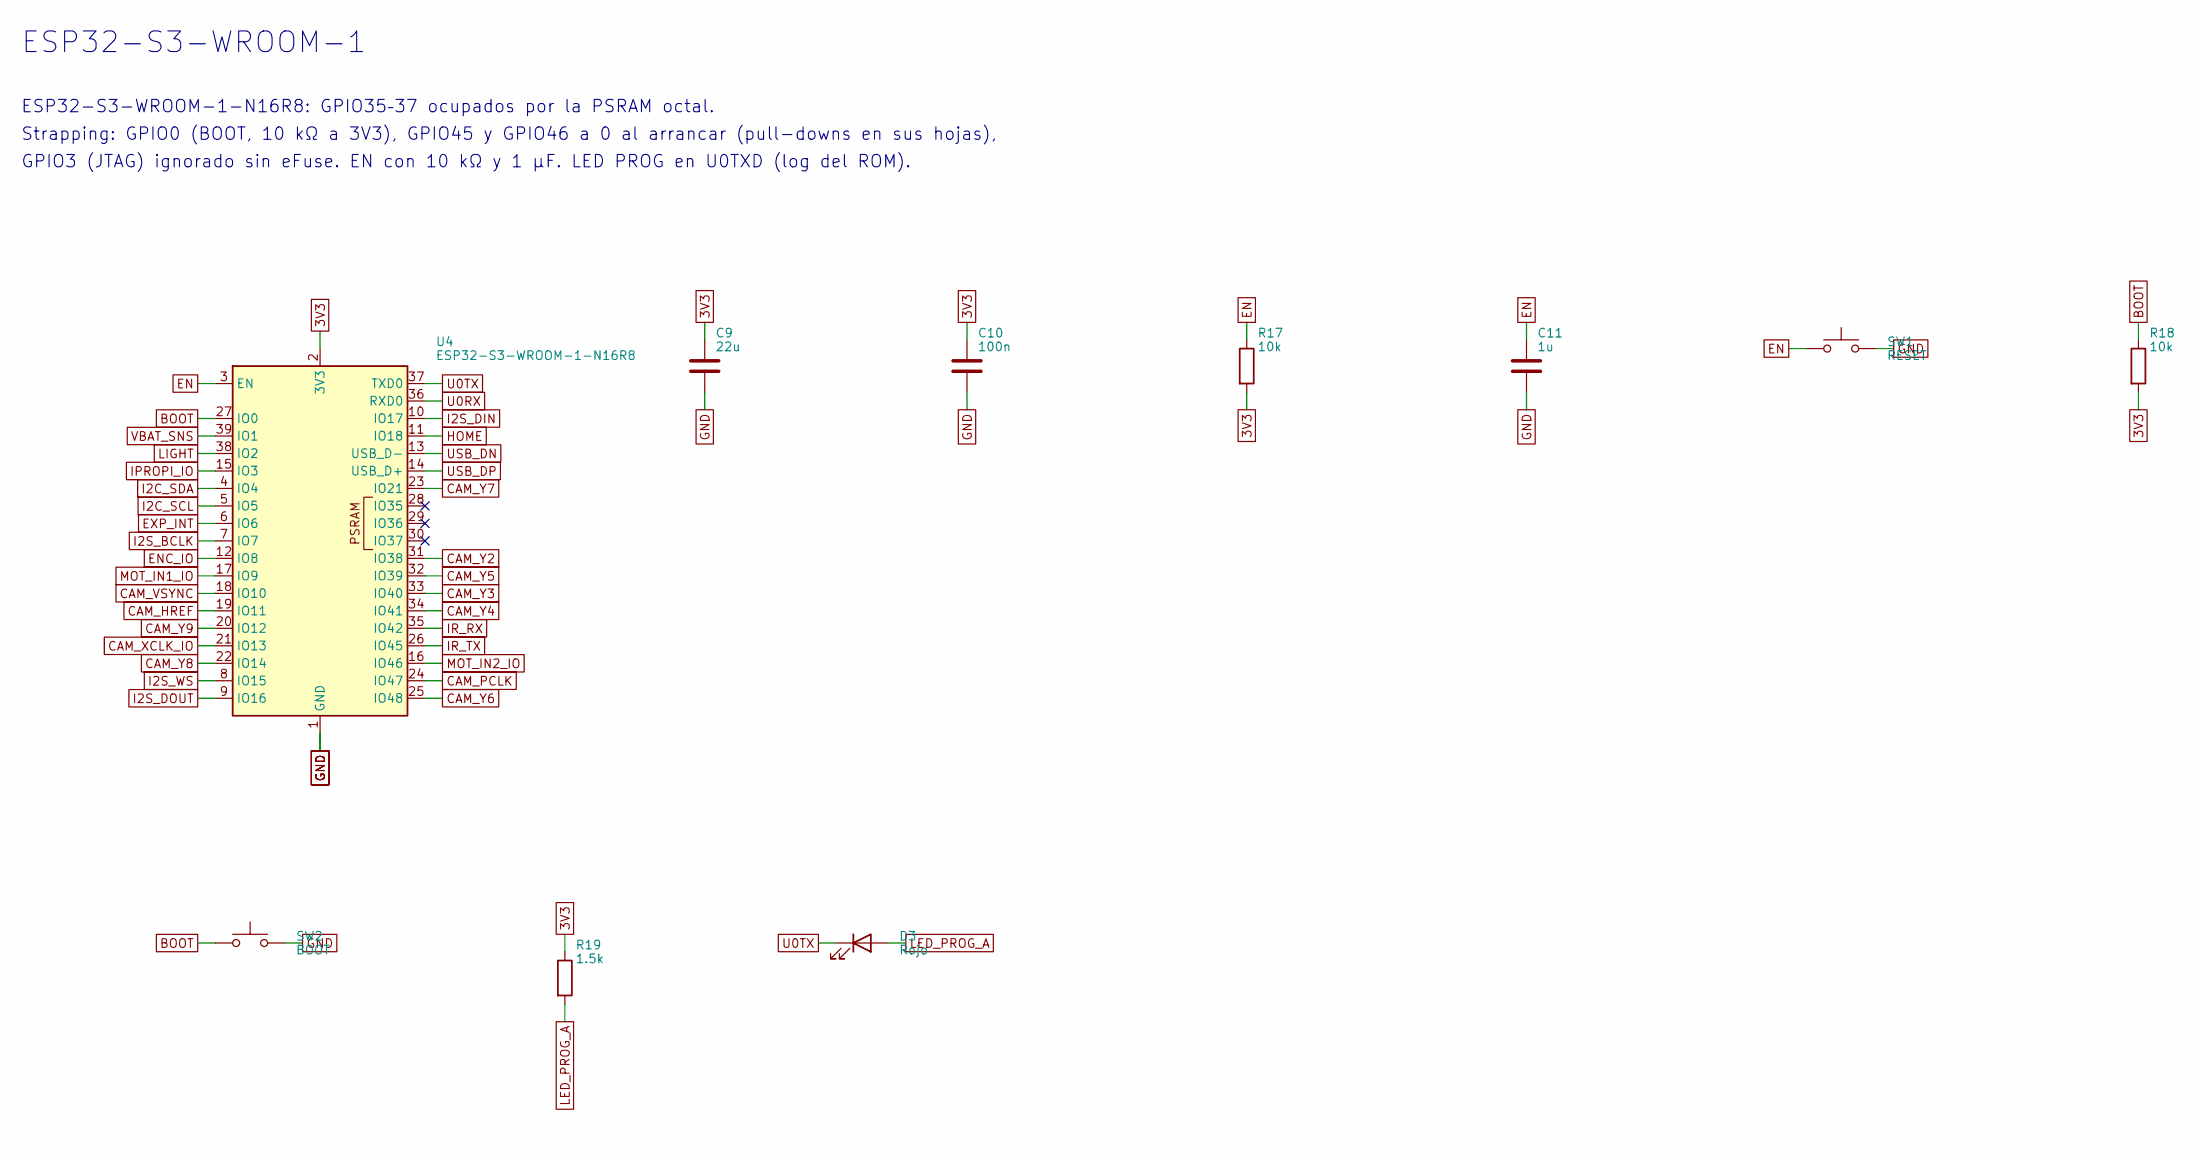
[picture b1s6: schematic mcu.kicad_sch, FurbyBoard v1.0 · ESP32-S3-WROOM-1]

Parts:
C9: 22u; C_0805_2012Metric; MPN 22 µF 25 V X5R; LCSC C45783
C10: 100n; C_0603_1608Metric; MPN 100 nF 50 V X7R; LCSC C14663
C11: 1u; C_0603_1608Metric; MPN 1 µF 50 V X5R; LCSC C15849
D3: Rojo; LED_0603_1608Metric; MPN KT-0603R; LCSC C2286
R17, R18: 10k; R_0603_1608Metric; MPN UNI-ROYAL 0603 1%; LCSC C25804
R19: 1.5k; R_0603_1608Metric; MPN UNI-ROYAL 0603 1%; LCSC C22843
SW1: RESET; SW_SPST_TS-1088-xR020; MPN TS-1088-AR02016; LCSC C720477
SW2: BOOT; SW_SPST_TS-1088-xR020; MPN TS-1088-AR02016; LCSC C720477
U4: ESP32-S3-WROOM-1-N16R8; ESP32-S3-WROOM-1; MPN Espressif ESP32-S3-WROOM-1-N16R8; LCSC C2913202

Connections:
3V3: C9.1, C10.1, R17.2, R18.2, R19.1, U4.2 (3V3); also elsewhere on the board
BOOT: R18.1, SW2.1, U4.27 (IO0)
CAM_HREF: U4.19 (IO11); also elsewhere on the board
CAM_PCLK: U4.24 (IO47); also elsewhere on the board
CAM_VSYNC: U4.18 (IO10); also elsewhere on the board
CAM_XCLK_IO: U4.21 (IO13); also elsewhere on the board
CAM_Y2: U4.31 (IO38); also elsewhere on the board
CAM_Y3: U4.33 (IO40); also elsewhere on the board
CAM_Y4: U4.34 (IO41); also elsewhere on the board
CAM_Y5: U4.32 (IO39); also elsewhere on the board
CAM_Y6: U4.25 (IO48); also elsewhere on the board
CAM_Y7: U4.23 (IO21); also elsewhere on the board
CAM_Y8: U4.22 (IO14); also elsewhere on the board
CAM_Y9: U4.20 (IO12); also elsewhere on the board
EN: C11.1, R17.1, SW1.1, U4.3 (EN)
ENC_IO: U4.12 (IO8); also elsewhere on the board
EXP_INT: U4.6 (IO6); also elsewhere on the board
GND: C9.2, C10.2, C11.2, SW1.2, SW2.2, U4.1 (GND), U4.40 (GND), U4.41 (GND); also elsewhere on the board
HOME: U4.11 (IO18); also elsewhere on the board
I2C_SCL: U4.5 (IO5); also elsewhere on the board
I2C_SDA: U4.4 (IO4); also elsewhere on the board
I2S_BCLK: U4.7 (IO7); also elsewhere on the board
I2S_DIN: U4.10 (IO17); also elsewhere on the board
I2S_DOUT: U4.9 (IO16); also elsewhere on the board
I2S_WS: U4.8 (IO15); also elsewhere on the board
IPROPI_IO: U4.15 (IO3); also elsewhere on the board
IR_RX: U4.35 (IO42); also elsewhere on the board
IR_TX: U4.26 (IO45); also elsewhere on the board
LED_PROG_A: D3.2 (A), R19.2
LIGHT: U4.38 (IO2); also elsewhere on the board
MOT_IN1_IO: U4.17 (IO9); also elsewhere on the board
MOT_IN2_IO: U4.16 (IO46); also elsewhere on the board
U0RX: U4.36 (RXD0); also elsewhere on the board
U0TX: D3.1 (K), U4.37 (TXD0); also elsewhere on the board
USB_DN: U4.13 (USB_D-); also elsewhere on the board
USB_DP: U4.14 (USB_D+); also elsewhere on the board
VBAT_SNS: U4.39 (IO1); also elsewhere on the board

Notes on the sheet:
GPIO3 (JTAG) ignorado sin eFuse. EN con 10 kΩ y 1 µF. LED PROG en U0TXD (log del ROM).
Strapping: GPIO0 (BOOT, 10 kΩ a 3V3), GPIO45 y GPIO46 a 0 al arrancar (pull-downs en sus hojas),
ESP32-S3-WROOM-1
ESP32-S3-WROOM-1-N16R8: GPIO35–37 ocupados por la PSRAM octal.
